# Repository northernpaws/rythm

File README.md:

> Rythm is now Catalina!

# Catalina

> ⚠️ This is still a large work-in-progress! A semi-working version (hardware and software) is estimated to be ready around March 2026.

Catalina is an embedded-first Rust ecosystem for building music and audio processing devices, with a primary focus on ARM Cortex MCUs as the end-target.

The ecosystem is comprised of:
 * A Rust crate providing a DSP and audio engine designed for embedded devices (heapless by default, small footprint).
   * Various composable interfaces for quickly prototyping new instruments.
   * Drivers for common audio codecs, SDRAM, etc.
   * Windows, MacOS, and Linux support for developing audio chains before flashing to hardware.
   * Future web interface for synth design, with WebUSB for direct device flashing.
 * Two base hardware modules designed for the engine:
   * **Mini** - small footprint with audio processing.
   * **Card** - larger footprint with audio processing, CV and sync.
 * Several module "carrier" boards:
   * Breadboard-compatible carrier with headers.
   * Protoboard-style carrier with an integrated module.
 * Potentially some future soldering kits.
 * A Rust BSP (Board cupport package) crate that makes it easy to get started with any modules or boards from the ecosystem.

## TODO

  * [ ] Finish Mini module revision 1.
  * [ ] Finish Card module revision 2.
  * [ ] Stable minor release of `engine`, with audio and synth basic building blocks.

# Engine

`catalina-engine` is a set of embedded-first DSP and audio engine crates that can be quickly integrated into embedded projects as a dependency, or used standalone with the std library for audio application.

The engine crates are designed to be as modular as possible, so i.e. if you just need a couple oscillators, you can use the oscillator module without needed to depend on any other parts of the engine. This composability is designed to make building audio effects and instruments as intuitive as possible.

The engine supports both the `core` embedded and `std` runtimes, including support for common embedded loggers (`defmt`, `log`), embedded and std library `tracing`, `std` and `alloc` feature sets from underlying libraries, and more via crate feature flags.

> Note! As the engine is embedded-first, `no_std` is set by feature flags by default. You'll need to manually enable the `std` feature to toggle off the default `no_std` declaration. 

Our goal is to make the usage of the engine as seamless as possible across both embedded and non-embedded platforms, making prototyping designs on PC and in simulators, and then later transferring them to embedded device runtimes as easy as possible.

# Modules

> ⚠️ The modules and their associated boards are a large work-in-progress! Several designs are only half-complete or still in the planning stages.

The modules provides a set of small STM32-based boards that can be embedded into custom PCB designs, or used with a set of associated carrier boards.

These carrier boards include basic breadboard header breakouts, some module-integrated protoboard designs, and some options for carriers with a selection of [Molex PicoBlade Connectors](https://www.molex.com/en-us/products/connectors/wire-to-board-connectors/picoblade-connectors) for modular plug-and-play prototyping.

Also see furthur in the README for kits that are designed as self-assembled soldering kits that let you quickly get started creating guitar/effects pedals, and small synths and sequencers using the toolkit.

> ⚠️ The ecosystem's modules are **NOT** able to be used standalone, they only have fine-pitch [Hirose DF40C board-to-board connectors](https://www.hirose.com/en/product/document?clcode=&productname=&series=DF40&documenttype=Catalog&lang=en&documentid=en_DF40_CAT) - a carrier board is required to interface with them!
>
> See our upcoming carriers or soldering kits below for examples.

## Mini

|   |  |  |
|:---:|:---:|:---:|

> ⚠️ Mini is in active design, these images may be out of date.

**[Schematic Viewer](https://kicanvas.org/?github=https%3A%2F%2Fgithub.com%2Fnorthernpaws%2Fcatalina%2Ftree%2Fmain%2Fhardware%2Fboards%2Fmini%2Fv0.2)**

  * 480MHz ARM Cortex-M7 processor (STM32H750XBHx)
  * 32MB of 16-bit SDRAM for audio buffers
  * 16MB QSPI Flash for programs and settings
  * 24-bit Stereo Audio Codec with internal mixer
  * SDMMC 4-bit interface
  * 1 Hardware MIDI Endpoint (RX and TX)

The Mini is a 20mm x 40mm module, designed to have a similar footprint to an Arduino Nano to make it easy to fit in a variaty of small audio and music devices. The Mini also has a breadboard-compatible carrier that exposes 2 columns of breadboard pins on either side of the carrier on standard 5-5 breadboard column layouts.

The mini is ideal for applications that don't need a large amount of audio RAM and need to fit in a small footprint - such as a guitar/effects pedal, Altoids tin, or 2HP Eurorack modules similar to [Erica Synths' Pico series](https://www.ericasynths.lv/shop/eurorack-modules/by-series/pico-series/).

### TODO

  * ~~[ ] In Revision 3, see if we can switch to SDMMC2 to enable both QSPI 1 and 2 simultaneously to expose one over the connector.~~
  * [x] *Or connect PG6 (`QUADSPI_BK1_NCS`) to connector, connect QUADSPI1 to connector, and provide a bootloader toggle that allows the carrier to indicate it should use carrier select pin.*
  * [ ] Determine values of remaining unspecified resistors and capacitors.
  * [ ] Calculate ideal HSE oscillator for the STM32H750.
  * [ ] Finish BOM selection for crystal, some resistors and capacitors.
  * [ ] Hirose DF40 connectors are now not recommended for dual-connector use. Despite still working for it, I don't feel comfortable going against manufacture recommendations for reliability reasons. For revision 3 we need to change to a single connector, possibly by shifting the MCU and RAM up or down to make room for a longer connector at 90 degrees on the bottom.

### Revision History

 * v0.1 - Original design with a BGA201 package. Ran into too many trace tollerance issues on fan-out, so had to upgrade to the BGA265 package to have enough room to run traces between via-in-pads and to do dogbones.
 * v0.2 - Changed to BGA 265, but layout changes from the 201 to 265 made x32 SDRAM layout near impossible. Switched to a 16mx16 SDRAM instead, which should be sufficient for the Mini. 
 * v0.3 - Found possible alignment and tolerance issues with mating 2x Hirose DF40 connectors, so shifted the MCU and codec to change the dual connectors for a single high-density one. Used DF40-90DP to have sufficient pins available, and because the 90-pin is more widely available.

### Notes

 * Mini was originally designed with the BGA201 package, but the pitch was too fine for economic fabrication capabilities. Upgraded to BGA265 in revision 2 to fix routing constraints. 
 * The Mini's original design concept was using 16mx32 SDRAM, with 32-bit SDRAM being ideal for handling encoding of stereo 16-bit audio samples (one 32-bit byte per stereo sample). Ultimately there was not enough room for routing x32 SDRAM with STM32's non-standard memory interface ball out, so a compromise to use 16-bit instead was made to keep the mini at in our 20mm wide constraint. 

## Card

> ⚠️ The card module is only in the planning stage.

Everything from the Mini:

  * 480MHz ARM Cortex-M7 processor
  * QSPI Flash
  * Stereo Audio Codec
  * SDMMC 4-bit interface

Plus:

  * 64MB of 32-bit SDRAM (4 times the amount on the Mini!)
  * Eurorack CV inputs (amount TBD)
  * Eurorack CV outputs (amount TBD)
  * Eurorack Sync In/Out (amount TBD)

The Card module is larger then the Mini, about the size of a credit card. It also features a different board-to-board connector from the Mini, supporting much higher board-to-board distances allowing it to seat over top of higher components (i.e. 3.5mm audio sockets) then the Mini can.

The Card is designed for audio applications that need significantly more memory, and benefit from having 32-bit memory (such as faster access for stereo 16-bit samples), like hardware samplers. The Card also features an onboard bank of dynamic CV sink, input, and output drivers that allow it to function as a Eurorack module off-the-shelf, or with synths and sequencers that have control voltage sockets.

### TODO

  * [ ] Ensure we can route a full 16mx32 SDRAM in the Card footprint.
  * [ ] Research the best CV circuits we can use to support a large range of biasing and voltages (i.e. -12v to +12v).
  * [ ] After SDRAM routing, can we break the parallel interface out to a B2B connector? Could be useful for driving displays, or memory expension with additional chips.
  * [ ] Aim to break out one of the QSPI interfaces so carriers can add additional flash. One ideas is for Card carriers to have their own carrier-specific flash that the module can load when attached, so programs don't need to be reflashed if sharing a module across carriers.
  * [ ] Uses DF40TC for higher range of hight offset. Maximum of 7mm allows mounting the module over most 3.5mm and USB sockets. DF40TC(3.0)-50DP-0.4V(51) as base, with: DF40TC-##DS-0.4V(51)   = 4.5 (min), DF40TC(4.0)-##DS-0.4V(51)  = 7.0mm (max).

# Carriers

Carriers are breakout boards for the core modules that make them easy to prototype and work with, without needing to make a custom board for their dense board-to-board connectors. 

Some of the planned carriers are:

  * "Discovery" line that breaks the module's IO's out to standard breadboard compatible pin headers. Includes a USB-C port for device and host mode, contains an ARM Cortex programming header keyed for an IDC cable, and possibly an SD card. Includes the required electrolytic capacitors for the integrated headphone driver on the modules.
  * "Proto" line that has a protoboard layout with a socket for the module in the center, making it easy to not only prototype more stable circuits directly with the module, but also to unsocket and swap the module between multiple proto boards so you don't need to buy several for different projects.

And a couple other ideas that need to be planned out:
  * A carrier that breaks out the audio and MIDI lines as 3.5mm sockets, and IO on [Molex PicoBlade connectors](https://www.google.com/search?client=safari&rls=en&q=picoblade+connector&ie=UTF-8&oe=UTF-8) for rapid modular prototyping (maybe use the "Discovery" name for this one instead?). 

## TODO
  * FUSB303BTMX on discovery for USB-C support
  * Amphenol_12401610E4-2A or HRO_TYPE-C-31-M-12?

# Kits

The hardware ecosystem will also include several soldering kits that are currently in various stages of development:
 * **Mini Module**
   * **Guitar/Effects Pedal Kit** - PCB with several connectors for knobs and foot switches, includes some knob and footswitch options, a Mini module, and 
   * **Mini Synth Kit** - A carrier similar to the Korg Volca or Behringer Pro series with a capacitive keyboard, several knobs and buttons, and 3.5mm MIDI minijack. Comes with a few printed faceplates and a 3D printed case. Carrier sockets could be solderable in kit form.
   * **Mini Step Sequencer Kit** - A small step or drum sequencer design, similar to the Roland AIRA Compact or Elektron Model lineup. Buttons and knobs solderable for kit form.
   * **Mini Groovebox Kit** - Something similar to an Elektron Model or Novation Circuit series device. A 4x8 velocity pad grid (velostat?), several knobs, and some menu buttons.
 * **Card Module**
   * **Eurorack Module Kit** - A 4-8 HP (to be determined) Eurorack carrier sporting all the Card CV inputs and outputs as standard 3.5mm sockets, USB, 3.5mm MIDI Minijack and an SD card.
   * **Pro Synth Kit** - Similar to the Midi Synth Kit, but also sporting a display, more control, and 3.5mm CV sockets.
   * **Pro Step Sequencer Kit** - Something similar to an Elektron Digitakt, SEQTRAK, or Korg SQ-1 with 16-step buttons, a display, and some knobs.

Each of these kits will come with a board support package via a feature flag in the Rust crate. These board support packages will come with all the scaffolding necessary to quickly build a project around the boards, as well as several example projects. 

# Supporters

Thank you to the supporters that helped design and fund this project!

It would not have been possible for me to spend the time or funds on making this without their support.

 * [Rachel Mant (@dragonmux)](https://github.com/dragonmux)
 * [Aki (@lethalbit)](https://github.com/lethalbit)
 * [Luna Rabbit (@LunaUsagi)](https://lunarabbit.moe)
 * [Sludge (@SludgeGirl)](https://github.com/SludgeGirl)
 * [Esden (@esden)](https://github.com/esden)
 * [Miika (@nykseli)](https://github.com/Nykseli)
 * Freyja
 * [Mary Guillemard (@marysaka)](https://github.com/marysaka)
 * [3cats](https://tokilabs.co)

If you would like to support this project, see either my [GitHub Sponsors page](https://github.com/sponsors/northernpaws) or [Patreon](https://www.patreon.com/cw/Northernpaws).

Support includes access to exclusive Discord channels with sneak peaks and design discussions.

# License

The hardware and CAD components of this project are licensed under the CERN Open Hardware License v2.0. The particular of the CERN-OHL license (permissive, weakly reciprocal, strongly reciprocal) can very depending on the hardware component and should be checked on a per-component basis by finding the closest LICENSE file to it.

The software components of this project are under the MIT license.

Concepts, such as the pin arrangement of the high-density connectors on the modules is consided free and open to build on, especially if you're looking to make a carrier board or product!

`SPDX-License-Identifier: CERN-OHL-S-2.0 AND MIT`

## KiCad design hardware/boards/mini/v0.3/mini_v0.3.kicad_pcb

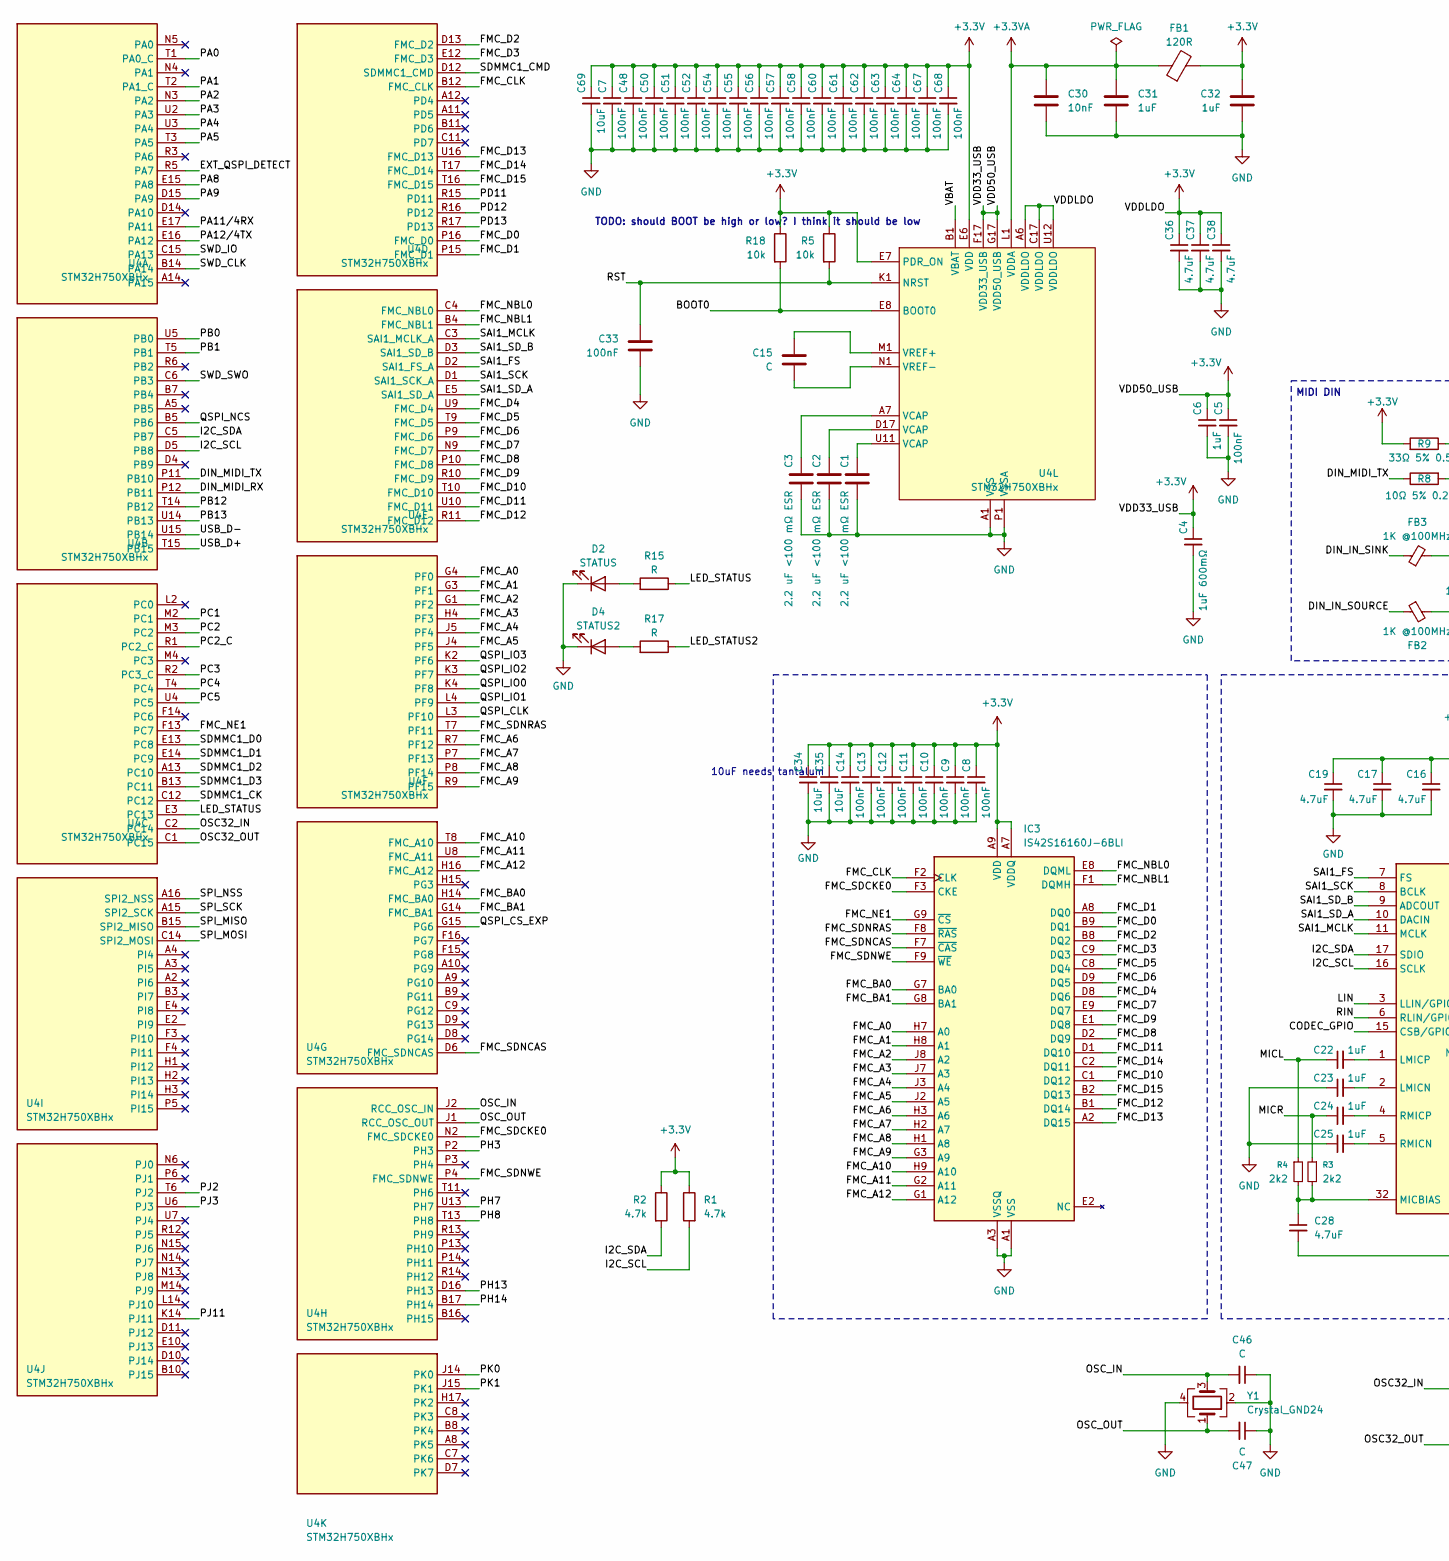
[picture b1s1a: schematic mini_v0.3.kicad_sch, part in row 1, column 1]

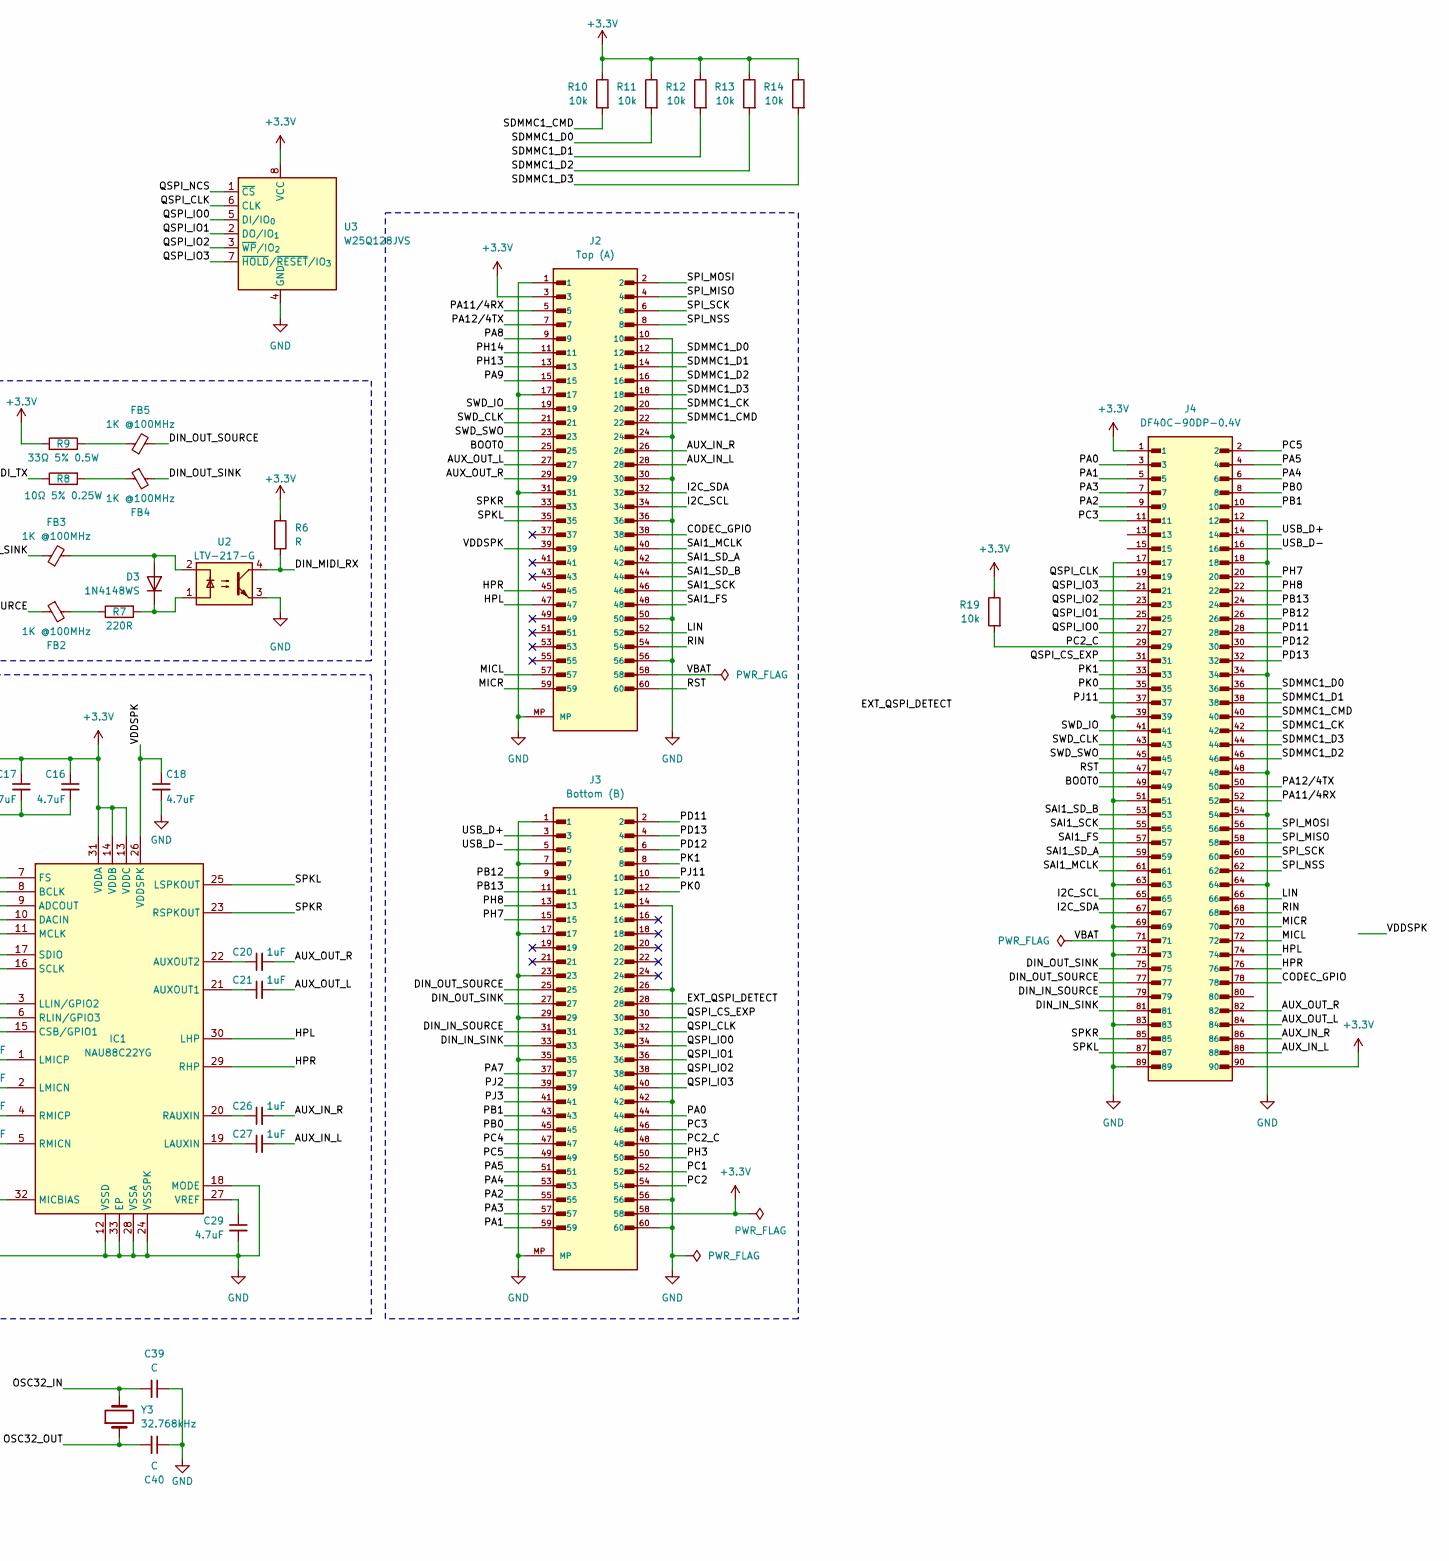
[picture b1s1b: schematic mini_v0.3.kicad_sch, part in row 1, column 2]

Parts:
C1, C2, C3: 2.2 uF <100 mΩ ESR; C_0402_1005Metric; LCSC C170151
C4: 1uF 600mΩ; C_0402_1005Metric; LCSC C14445
C5, C7, C8, C9, C10, C11, C12, C13, C14, C33, C48, C50, C51, C52, C54, C55, C56, C57, C58, C60, C61, C62, C63, C64, C67, C68: 100nF; C_0402_1005Metric; LCSC C3015120
C6, C20, C21, C22, C23, C24, C25, C26, C27, C31, C32: 1uF; C_0402_1005Metric; LCSC C3833440
C15, C39, C40, C46, C47: C; C_0402_1005Metric
C16, C17, C18, C19, C28, C29, C36, C37, C38: 4.7uF; C_0402_1005Metric; LCSC C2986065
C30: 10nF; C_0402_1005Metric; LCSC C1852256
C34, C35, C69: 10uF; C_0402_1005Metric; LCSC C315248
D2: STATUS; LED_0603_1608Metric
D3: 1N4148WS; D_SOD-323
D4: STATUS2; LED_0603_1608Metric
FB1: 120R; L_0402_1005Metric; LCSC C76891
FB2, FB3, FB4, FB5: 1K @100MHz; L_0402_1005Metric; LCSC C76889
IC1: NAU88C22YG; QFN-32-1EP_5x5mm_P0.5mm_EP3.6x3.6mm; Mouser Part Number 503-NAU88C22YG
IC3: IS42S16160J-6BLI; Alliance_TFBGA-54_8x8mm_Layout9x9_P0.8mm; Manufacturer_Part_Number IS42S16160J-6BLI; Mouser Part Number 870-42S16160J6BLI
J2: Top (A); Hirose_DF40C-60DP-0.4V_2x30-1MP_P0.4mm; PARTREV 8; LCSC C424647
J3: Bottom (B); Hirose_DF40C-60DP-0.4V_2x30-1MP_P0.4mm; PARTREV 8; LCSC C424647
J4: DF40C-90DP-0.4V; Hirose_DF40C-90DP-0.4V_2x45-1MP_P0.4mm; PARTREV 8; DigiKey_Part_Number H11614CT-ND
R1, R2: 4.7k; R_0402_1005Metric; LCSC C105871
R3, R4: 2k2; R_0402_1005Metric; LCSC C114762
R5, R10, R11, R12, R13, R14, R18, R19: 10k; R_0402_1005Metric; LCSC C60490
R6, R15, R17: R; R_0402_1005Metric
R7: 220R; R_0402_1005Metric; LCSC C112291
R8: 10Ω 5% 0.25W; R_0402_1005Metric
R9: 33Ω 5% 0.5W; R_0402_1005Metric
U2: LTV-217-G; SOIC-4_4.55x2.6mm_P1.27mm; LCSC C17407902
U3: W25Q128JVS; SOIC-8_5.3x5.3mm_P1.27mm
U4: STM32H750XBHx; TFBGA-265_14x14mm_Layout17x17_P0.8mm; LCSC C405932
Y1: Crystal_GND24; Crystal_SMD_Abracon_ABM10-4Pin_2.5x2.0mm
Y3: 32.768kHz; Crystal_SMD_3215-2Pin_3.2x1.5mm; LCSC C32346

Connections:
+3.3V: C4.1, C5.1, C6.1, C7.1, C8.1, C9.1, C10.1, C11.1, C12.1, C13.1, C14.1, C16.1, C17.1, C19.1, C32.1, C34.1, C35.1, C36.1, C37.1, C38.1, C48.1, C50.1, C51.1, C52.1, C54.1, C55.1, C56.1, C57.1, C58.1, C60.1, C61.1, C62.1, C63.1, C64.1, C67.1, C68.1, C69.1, FB1.2, IC1.13 (VDDC), IC1.14 (VDDB), IC1.31 (VDDA), IC3.A7 (VDDQ), IC3.A9 (VDD), IC3.B3 (VDDQ), IC3.C7 (VDDQ), IC3.D3 (VDDQ), IC3.E7 (VDD), IC3.J9 (VDD), J2.3, J3.58, J4.1, J4.90, R1.1, R2.1, R5.1, R6.1, R9.2, R10.1, R11.1, R12.1, R13.1, R14.1, R18.1, R19.1, U3.8 (VCC), U4.A6 (VDDLDO), U4.C17 (VDDLDO), U4.E6 (VDD), U4.E7 (PDR_ON), U4.E9 (VDD), U4.E11 (VDD), U4.F5 (VDD), U4.F17 (VDD33_USB), U4.G5 (VDD), U4.G13 (VDD), U4.G17 (VDD50_USB), U4.H5 (VDD), U4.H13 (VDD), U4.J13 (VDD), U4.K5 (VDD), U4.K13 (VDD), U4.L5 (VDD), U4.L13 (VDD), U4.M5 (VDD), U4.M13 (VDD), U4.N7 (VDD), U4.N8 (VDD), U4.N10 (VDD), U4.N11 (VDD), U4.N12 (VDD), U4.P17 (VDD), U4.U12 (VDDLDO)
+3.3VA: C30.1, C31.1, FB1.1, U4.L1 (VDDA)
/AUX_IN_L: C27.2, J2.28, J4.88
/AUX_IN_R: C26.2, J2.26, J4.86
/AUX_OUT_L: C21.2, J2.27, J4.84
/AUX_OUT_R: C20.2, J2.29, J4.82
/BOOT0: J2.25, J4.49, R18.2, U4.E8 (BOOT0)
/CODEC_GPIO: IC1.15 (CSB/GPIO1), J2.38, J4.78
/DIN_IN_SINK: FB3.1, J3.33, J4.81
/DIN_IN_SOURCE: FB2.1, J3.31, J4.79
/DIN_MIDI_RX: R6.2, U2.4, U4.P12 (PB11)
/DIN_MIDI_TX: R8.1, U4.P11 (PB10)
/DIN_OUT_SINK: FB4.2, J3.27, J4.75
/DIN_OUT_SOURCE: FB5.2, J3.25, J4.77
/EXT_QSPI_DETECT: J3.28, U4.R5 (PA7)
/FMC_A0: IC3.H7 (A0), U4.G4 (PF0)
/FMC_A1: IC3.H8 (A1), U4.G3 (PF1)
/FMC_A2: IC3.J8 (A2), U4.G1 (PF2)
/FMC_A3: IC3.J7 (A3), U4.H4 (PF3)
/FMC_A4: IC3.J3 (A4), U4.J5 (PF4)
/FMC_A5: IC3.J2 (A5), U4.J4 (PF5)
/FMC_A6: IC3.H3 (A6), U4.R7 (PF12)
/FMC_A7: IC3.H2 (A7), U4.P7 (PF13)
/FMC_A8: IC3.H1 (A8), U4.P8 (PF14)
/FMC_A9: IC3.G3 (A9), U4.R9 (PF15)
/FMC_A10: IC3.H9 (A10), U4.T8 (FMC_A10)
/FMC_A11: IC3.G2 (A11), U4.U8 (FMC_A11)
/FMC_A12: IC3.G1 (A12), U4.H16 (FMC_A12)
/FMC_BA0: IC3.G7 (BA0), U4.H14 (FMC_BA0)
/FMC_BA1: IC3.G8 (BA1), U4.G14 (FMC_BA1)
/FMC_CLK: IC3.F2 (CLK), U4.B12 (FMC_CLK)
/FMC_D0: IC3.B9 (DQ1), U4.P16 (FMC_D0)
/FMC_D1: IC3.A8 (DQ0), U4.P15 (FMC_D1)
/FMC_D2: IC3.B8 (DQ2), U4.D13 (FMC_D2)
/FMC_D3: IC3.C9 (DQ3), U4.E12 (FMC_D3)
/FMC_D4: IC3.D8 (DQ6), U4.U9 (FMC_D4)
/FMC_D5: IC3.C8 (DQ4), U4.T9 (FMC_D5)
/FMC_D6: IC3.D9 (DQ5), U4.P9 (FMC_D6)
/FMC_D7: IC3.E9 (DQ7), U4.N9 (FMC_D7)
/FMC_D8: IC3.D2 (DQ9), U4.P10 (FMC_D8)
/FMC_D9: IC3.E1 (DQ8), U4.R10 (FMC_D9)
/FMC_D10: IC3.C1 (DQ12), U4.T10 (FMC_D10)
/FMC_D11: IC3.D1 (DQ10), U4.U10 (FMC_D11)
/FMC_D12: IC3.B1 (DQ14), U4.R11 (FMC_D12)
/FMC_D13: IC3.A2 (DQ15), U4.U16 (FMC_D13)
/FMC_D14: IC3.C2 (DQ11), U4.T17 (FMC_D14)
/FMC_D15: IC3.B2 (DQ13), U4.T16 (FMC_D15)
/FMC_NBL0: IC3.E8 (DQML), U4.C4 (FMC_NBL0)
/FMC_NBL1: IC3.F1 (DQMH), U4.B4 (FMC_NBL1)
/FMC_NE1: IC3.G9 (~CS), U4.F13 (PC7)
/FMC_SDCKE0: IC3.F3 (CKE), U4.N2 (FMC_SDCKE0)
/FMC_SDNCAS: IC3.F7 (~CAS), U4.D6 (FMC_SDNCAS)
/FMC_SDNRAS: IC3.F8 (~RAS), U4.T7 (PF11)
/FMC_SDNWE: IC3.F9 (~WE), U4.P4 (FMC_SDNWE)
/HPL: IC1.30 (LHP), J2.47, J4.74
/HPR: IC1.29 (RHP), J2.45, J4.76
/I2C_SCL: IC1.16 (SCLK), J2.34, J4.65, R1.2, U4.D5 (PB8)
/I2C_SDA: IC1.17 (SDIO), J2.32, J4.67, R2.2, U4.C5 (PB7)
/LED_STATUS: R15.1, U4.E3 (PC13)
/LED_STATUS2: R17.1
/LIN: IC1.3 (LLIN/GPIO2), J2.52, J4.66
/MICL: C22.1, J2.57, J4.72, R4.1
/MICR: C24.1, J2.59, J4.70, R3.1
/OSC32_IN: C39.2, U4.C2 (PC14), Y3.2
/OSC32_OUT: C40.2, U4.C1 (PC15), Y3.1
/OSC_IN: C46.2, U4.J2 (RCC_OSC_IN), Y1.3
/OSC_OUT: C47.2, U4.J1 (RCC_OSC_OUT), Y1.1
/PA0: J3.44, J4.3, U4.T1 (PA0_C)
/PA1: J3.59, J4.5, U4.T2 (PA1_C)
/PA2: J3.55, J4.9, U4.N3 (PA2)
/PA3: J3.57, J4.7, U4.U2 (PA3)
/PA4: J3.53, J4.6, U4.U3 (PA4)
/PA5: J3.51, J4.4, U4.T3 (PA5)
/PA8: J2.9, U4.E15 (PA8)
/PA9: J2.15, U4.D15 (PA9)
/PA11/4RX: J2.5, J4.52, U4.E17 (PA11)
/PA12/4TX: J2.7, J4.50, U4.E16 (PA12)
/PB0: J3.45, J4.8, U4.U5 (PB0)
/PB1: J3.43, J4.10, U4.T5 (PB1)
/PB12: J3.9, J4.26, U4.T14 (PB12)
/PB13: J3.11, J4.24, U4.U14 (PB13)
/PC1: J3.52, U4.M2 (PC1)
/PC2: J3.54, U4.M3 (PC2)
/PC2_C: J3.48, J4.29, R19.2, U4.R1 (PC2_C)
/PC3: J3.46, J4.11, U4.R2 (PC3_C)
/PC4: J3.47, U4.T4 (PC4)
/PC5: J3.49, J4.2, U4.U4 (PC5)
/PD11: J3.2, J4.28, U4.R15 (PD11)
/PD12: J3.6, J4.30, U4.R16 (PD12)
/PD13: J3.4, J4.32, U4.R17 (PD13)
/PH3: J3.50, U4.P2 (PH3)
/PH7: J3.15, J4.20, U4.U13 (PH7)
/PH8: J3.13, J4.22, U4.T13 (PH8)
/PH13: J2.13, U4.D16 (PH13)
/PH14: J2.11, U4.B17 (PH14)
/PJ2: J3.39, U4.T6 (PJ2)
/PJ3: J3.41, U4.U6 (PJ3)
/PJ11: J3.10, J4.37, U4.K14 (PJ11)
/PK0: J3.12, J4.35, U4.J14 (PK0)
/PK1: J3.8, J4.33, U4.J15 (PK1)
/QSPI_CLK: J3.32, J4.19, U3.6 (CLK), U4.L3 (PF10)
/QSPI_CS_EXP: J3.30, J4.31, U4.G15 (PG6)
/QSPI_IO0: J3.34, J4.27, U3.5 (DI/IO_{0}), U4.K4 (PF8)
/QSPI_IO1: J3.36, J4.25, U3.2 (DO/IO_{1}), U4.L4 (PF9)
/QSPI_IO2: J3.38, J4.23, U3.3 (~WP/IO_{2}), U4.K3 (PF7)
/QSPI_IO3: J3.40, J4.21, U3.7 (~HOLD/~RESET/IO_{3}), U4.K2 (PF6)
/QSPI_NCS: U3.1 (~CS), U4.B5 (PB6)
/RIN: IC1.6 (RLIN/GPIO3), J2.54, J4.68
/RST: C33.1, J2.60, J4.47, R5.2, U4.K1 (NRST)
/SAI1_FS: IC1.7 (FS), J2.48, J4.57, U4.D2 (SAI1_FS_A)
/SAI1_MCLK: IC1.11 (MCLK), J2.40, J4.61, U4.C3 (SAI1_MCLK_A)
/SAI1_SCK: IC1.8 (BCLK), J2.46, J4.55, U4.D1 (SAI1_SCK_A)
/SAI1_SD_A: IC1.10 (DACIN), J2.42, J4.59, U4.E5 (SAI1_SD_A)
/SAI1_SD_B: IC1.9 (ADCOUT), J2.44, J4.53, U4.D3 (SAI1_SD_B)
/SDMMC1_CK: J2.20, J4.42, U4.C12
/SDMMC1_CMD: J2.22, J4.40, R10.2, U4.D12 (SDMMC1_CMD)
/SDMMC1_D0: J2.12, J4.36, R11.2, U4.E13 (PC8)
/SDMMC1_D1: J2.14, J4.38, R12.2, U4.E14 (PC9)
/SDMMC1_D2: J2.16, J4.46, R13.2, U4.A13 (PC10)
/SDMMC1_D3: J2.18, J4.44, R14.2, U4.B13 (PC11)
/SPI_MISO: J2.4, J4.58, U4.B15 (SPI2_MISO)
/SPI_MOSI: J2.2, J4.56, U4.C14 (SPI2_MOSI)
/SPI_NSS: J2.8, J4.62, U4.A16 (SPI2_NSS)
/SPI_SCK: J2.6, J4.60, U4.A15 (SPI2_SCK)
/SPKL: IC1.25 (LSPKOUT), J2.35, J4.87
/SPKR: IC1.23 (RSPKOUT), J2.33, J4.85
/SWD_CLK: J2.21, J4.43, U4.B14 (PA14)
/SWD_IO: J2.19, J4.41, U4.C15 (PA13)
/SWD_SWO: J2.23, J4.45, U4.C6 (PB3)
/USB_D+: J3.3, J4.14, U4.T15 (PB15)
/USB_D-: J3.5, J4.16, U4.U15 (PB14)
/VBAT: J2.58, J4.71, U4.B1 (VBAT)
/VDDSPK: C18.1, IC1.26 (VDDSPK), J2.39
GND: C1.2, C2.2, C3.2, C4.2, C5.2, C6.2, C7.2, C8.2, C9.2, C10.2, C11.2, C12.2, C13.2, C14.2, C16.2, C17.2, C18.2, C19.2, C23.1, C25.1, C28.2, C29.2, C30.2, C31.2, C32.2, C33.2, C34.2, C35.2, C36.2, C37.2, C38.2, C39.1, C40.1, C46.1, C47.1, C48.2, C50.2, C51.2, C52.2, C54.2, C55.2, C56.2, C57.2, C58.2, C60.2, C61.2, C62.2, C63.2, C64.2, C67.2, C68.2, C69.2, D2.1 (K), D4.1 (K), IC1.12 (VSSD), IC1.18 (MODE), IC1.24 (VSSSPK), IC1.28 (VSSA), IC1.33 (EP), IC3.A1 (VSS), IC3.A3 (VSSQ), IC3.B7 (VSSQ), IC3.C3 (VSSQ), IC3.D7 (VSSQ), IC3.E3 (VSS), IC3.J1 (VSS), J2.1, J2.10, J2.17, J2.24, J2.30, J2.31, J2.36, J2.50, J2.56, J2.MP, J3.1, J3.7, J3.14, J3.17, J3.23, J3.26, J3.29, J3.35, J3.42, J3.56, J3.60, J3.MP, J4.12, J4.17, J4.18, J4.34, J4.39, J4.48, J4.51, J4.54, J4.63, J4.64, J4.69, J4.73, J4.83, J4.89, U2.3, U3.4 (GND), U4.A1 (VSS), U4.A17 (VSS), U4.B2 (VSS), U4.B6 (VSS), U4.C10 (VSS), U4.C13 (VSS), U4.C16 (VSS), U4.F1 (VSS), U4.F2 (VSS), U4.G2 (VSS), U4.G7 (VSS), U4.G8 (VSS), U4.G9 (VSS), U4.G10 (VSS), U4.G11 (VSS), U4.G16 (VSS), U4.H7 (VSS), U4.H8 (VSS), U4.H9 (VSS), U4.H10 (VSS), U4.H11 (VSS), U4.J3 (VSS), U4.J7 (VSS), U4.J8 (VSS), U4.J9 (VSS), U4.J10 (VSS), U4.J11 (VSS), U4.J16 (VSS), U4.J17 (VSS), U4.K7 (VSS), U4.K8 (VSS), U4.K9 (VSS), U4.K10 (VSS), U4.K11 (VSS), U4.K15 (VSS), U4.L7 (VSS), U4.L8 (VSS), U4.L9 (VSS), U4.L10 (VSS), U4.L11 (VSS), U4.L15 (VSS), U4.M15 (VSS), U4.N16 (VSS), U4.P1 (VSSA), U4.R4 (VSS), U4.R8 (VSS), U4.T12 (VSS), U4.U1 (VSS), U4.U17 (VSS), Y1.2, Y1.4
unnamed: C1.1, U4.U11 (VCAP)
unnamed: C2.1, U4.D17 (VCAP)
unnamed: C3.1, U4.A7 (VCAP)
unnamed: D2.2 (A), R15.2
unnamed: D3.2 (A), FB3.2, U2.2
unnamed: D3.1 (K), R7.2, U2.1
unnamed: D4.2 (A), R17.2
unnamed: FB2.2, R7.1
unnamed: FB4.1, R8.2
unnamed: FB5.1, R9.1
unnamed: C21.1, IC1.21 (AUXOUT1)
unnamed: C20.1, IC1.22 (AUXOUT2)
unnamed: C27.1, IC1.19 (LAUXIN)
unnamed: C23.2, IC1.2 (LMICN)
unnamed: C22.2, IC1.1 (LMICP)
unnamed: C28.1, IC1.32 (MICBIAS), R3.2, R4.2
unnamed: C26.1, IC1.20 (RAUXIN)
unnamed: C25.2, IC1.5 (RMICN)
unnamed: C24.2, IC1.4 (RMICP)
unnamed: C29.1, IC1.27 (VREF)
unnamed: C15.1, U4.M1 (VREF+)
unnamed: C15.2, U4.N1 (VREF-)

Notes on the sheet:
TODO: should BOOT be high or low? I think it should be low
MIDI DIN
10uF needs tantalum

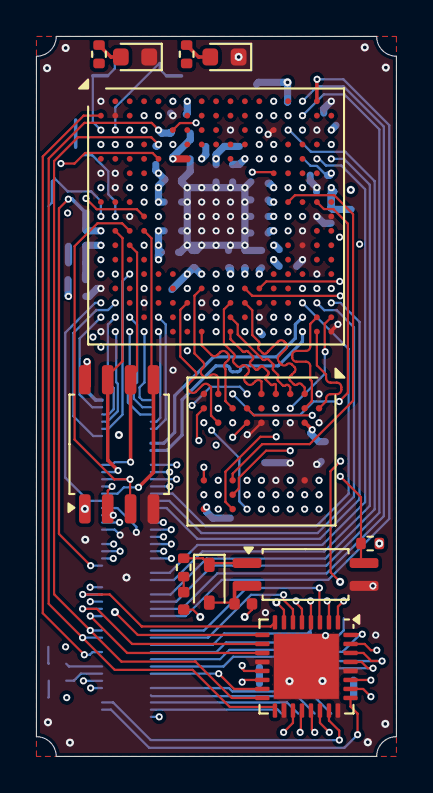
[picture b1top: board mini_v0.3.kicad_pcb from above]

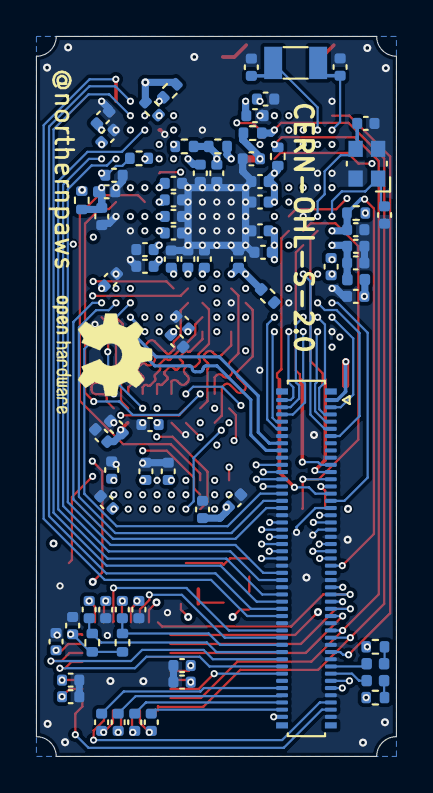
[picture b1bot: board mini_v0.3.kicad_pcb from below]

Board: 8 copper layers, 20.0 x 40.0 mm, 93 parts (79 on the bottom side), 144 nets.
